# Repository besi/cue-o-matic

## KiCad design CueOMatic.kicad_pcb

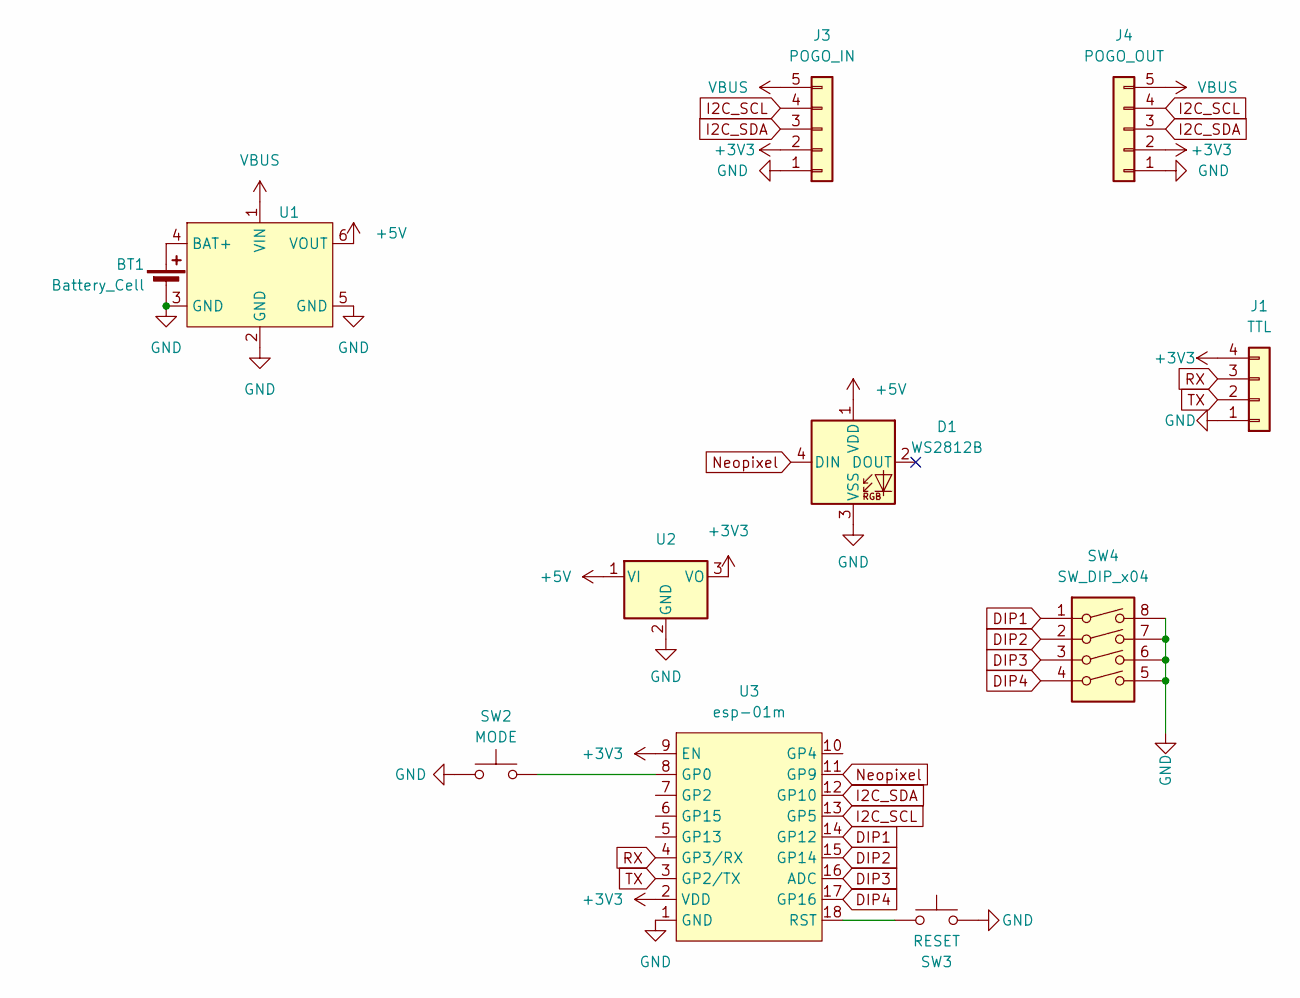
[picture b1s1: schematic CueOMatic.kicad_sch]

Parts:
BT1: Battery_Cell; JST_PH_B2B-PH-K_1x02_P2.00mm_Vertical
D1: WS2812B; LED_D5.0mm-4_RGB_Wide_Pins
J1: TTL; PinHeader_1x04_P2.54mm_Vertical
J3: POGO_IN; PinHeader_1x05_P2.54mm_Vertical
J4: POGO_OUT; PinHeader_1x05_P2.54mm_Vertical
SW2: MODE; pts636
SW3: RESET; pts636
SW4: SW_DIP_x04; SW_DIP_SPSTx04_Slide_6.7x11.72mm_W7.62mm_P2.54mm_LowProfile
U1: charge-module
U2: UA78M33_TO252; TO-252-2
U3: esp-01m

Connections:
+3V3: J1.4, J3.2, J4.2, U2.3 (VO), U3.2 (VDD), U3.9 (EN)
+5V: D1.1 (VDD), U1.6 (VOUT), U2.1 (VI)
DIP1: SW4.1, U3.14 (GP12)
DIP2: SW4.2, U3.15 (GP14)
DIP3: SW4.3, U3.16 (ADC)
DIP4: SW4.4, U3.17 (GP16)
GND: BT1.2 (-), D1.3 (VSS), J1.1, J3.1, J4.1, SW2.1, SW3.1, SW4.5, SW4.6, SW4.7, SW4.8, U1.2 (GND), U1.3 (GND), U1.5 (GND), U2.2 (GND), U3.1 (GND)
I2C_SCL: J3.4, J4.4, U3.13 (GP5)
I2C_SDA: J3.3, J4.3, U3.12 (GP10)
Neopixel: D1.4 (DIN), U3.11 (GP9)
unnamed: BT1.1 (+), U1.4 (BAT+)
unnamed: SW2.2, U3.8 (GP0)
unnamed: SW3.2, U3.18 (RST)
RX: J1.3, U3.4 (GP3/RX)
TX: J1.2, U3.3 (GP2/TX)
VBUS: J3.5, J4.5, U1.1 (VIN)

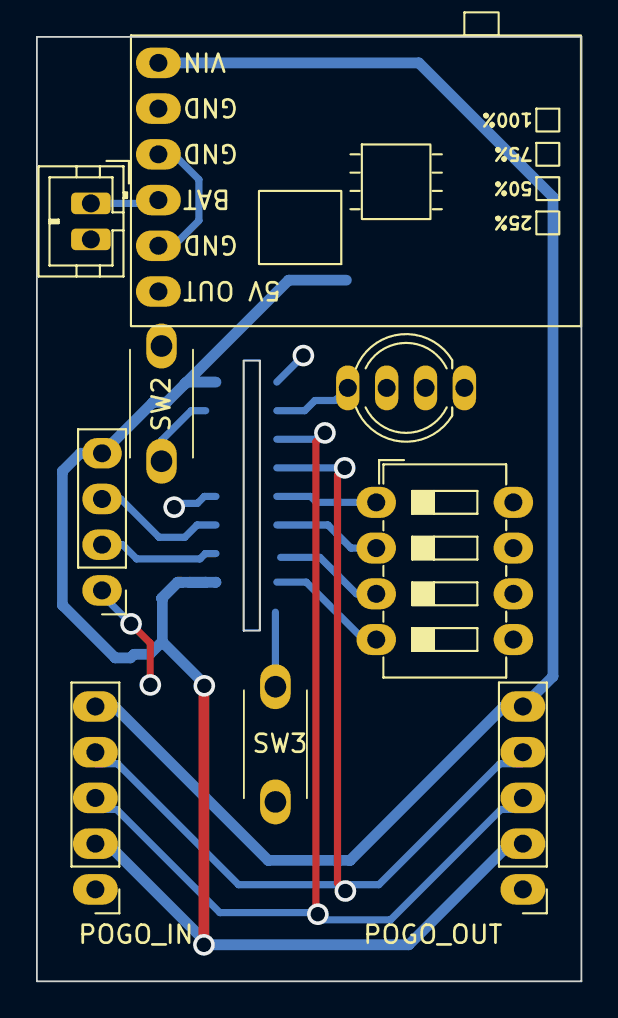
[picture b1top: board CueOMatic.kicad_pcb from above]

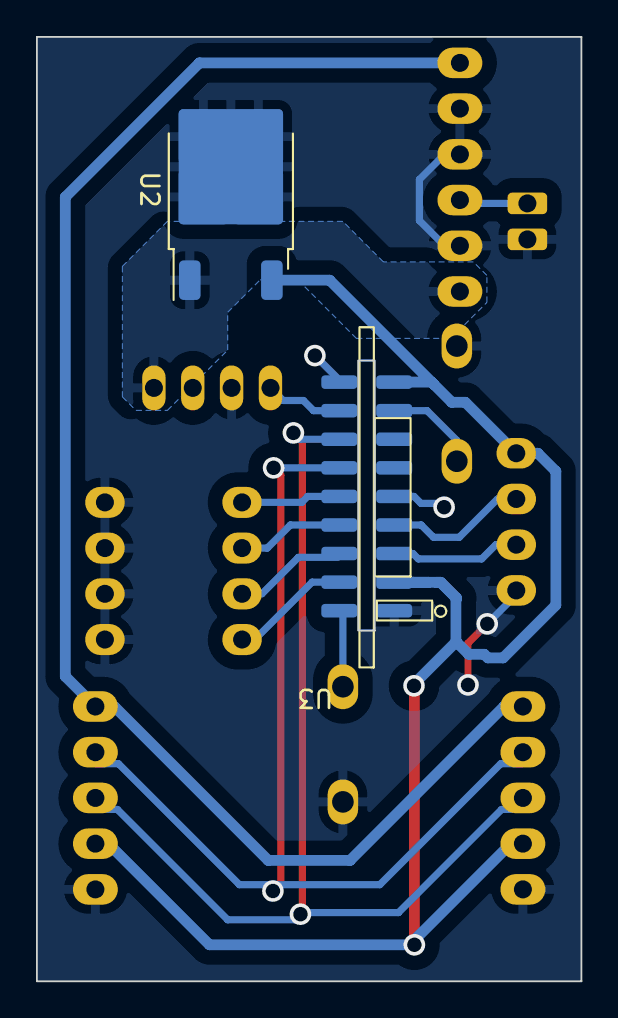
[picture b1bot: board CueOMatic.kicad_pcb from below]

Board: 2 copper layers, 30.2 x 52.4 mm, 11 parts (2 on the bottom side), 16 nets.

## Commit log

2024-03-09 Add mockup
2024-03-09 Initial PCB
2024-03-14 Pre milling
2024-03-14 Fabbing
2024-12-28 Schematic remarks
